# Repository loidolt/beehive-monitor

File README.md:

---
published: true
status: complete
date: 12/20/2016
tags: Electronics Outdoors
description: Beehive monitor that allows you to see the temperature and humidity of the hive.
slug: beehive-monitor
---

# Beehive Monitor

Beehive monitor that allows you to see the temperature and humidity of the hive.

## Table of Contents

- [Beehive Monitor](#beehive-monitor)
  - [Table of Contents](#table-of-contents)
  - [General Info](#general-info)
  - [Technologies](#technologies)

## General Info

This is is a beehive monitor that allows you to see the temperature and humidity of the hive. It also shows the general health of the hive using an LED strip based on ideal temperature and humidity values.

There are two temperature probes, one at the top of the hive and one that can be placed down by the hive ball to get a more accurate reading of the bees themselves. The temperature sensor at the top of the hive is also responsible for measuring humidity.

Sensor data is gathered once a minute, additionally, a rolling thirty-minute average is generated based on this data.

## Technologies
- SketchUp
- Eagle
- KiCAD
- Arduino

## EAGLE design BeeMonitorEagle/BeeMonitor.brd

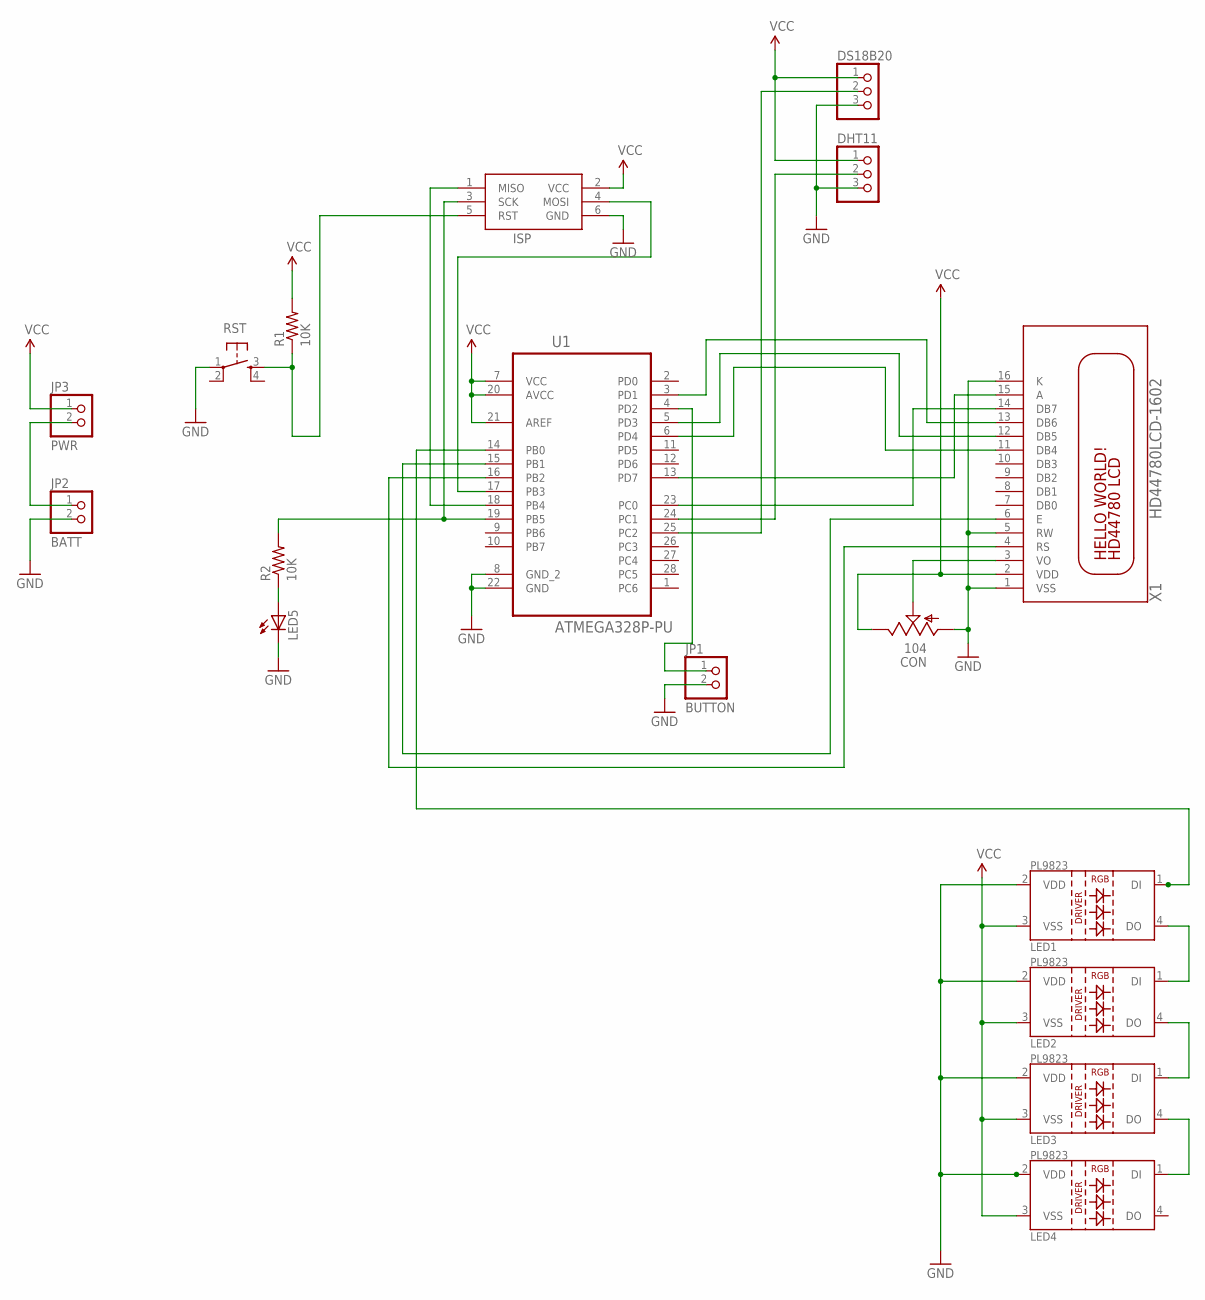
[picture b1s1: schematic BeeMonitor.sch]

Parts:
CON: 104; 6MM
DHT11: PINHD-1X3; 1X03
DS18B20: PINHD-1X3; 1X03
ISP: AVRISP-6; AVRISP
JP1: BUTTON; 1X02
JP2: BATT; 1X02
JP3: PWR; 1X02
LED1, LED2, LED3, LED4: LED-PL9823-F5
LED5: LED3MM
R1, R2: 10K; 0207/10
RST: TAC_SWITCHPTH; TACTILE-PTH
U1: ATMEGA328P-PU; DIP254P762X457-28
X1: HD44780LCD-1602; LCD1602

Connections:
GND: DHT11.3, DS18B20.3, ISP.6 (GND), JP1.2, JP2.2, LED1.2 (VDD), LED2.2 (VDD), LED3.2 (VDD), LED4.2 (VDD), LED5.K (C), RST.1, U1.8 (GND_2), U1.22 (GND)
unnamed: CON.S, X1.3 (VO)
unnamed: ISP.5 (RST), R1.1, RST.3
unnamed: ISP.3 (SCK), R2.2, U1.19 (PB5)
unnamed: ISP.1 (MISO), U1.18 (PB4)
unnamed: ISP.4 (MOSI), U1.17 (PB3)
unnamed: LED1.4 (DO), LED2.1 (DI)
unnamed: LED2.4 (DO), LED3.1 (DI)
unnamed: LED3.4 (DO), LED4.1 (DI)
unnamed: LED1.1 (DI), U1.14 (PB0)
unnamed: U1.3 (PD1), X1.13 (DB6)
unnamed: DHT11.2, U1.24 (PC1)
unnamed: DS18B20.2, U1.25 (PC2)
unnamed: JP1.1, U1.4 (PD2)
unnamed: U1.13 (PD7), X1.15 (A)
unnamed: U1.23 (PC0), X1.14 (DB7)
unnamed: U1.5 (PD3), X1.12 (DB5)
unnamed: U1.6 (PD4), X1.11 (DB4)
unnamed: U1.15 (PB1), X1.6 (E)
unnamed: U1.16 (PB2), X1.4 (RS)
unnamed: LED5.A, R2.1
unnamed: JP2.1, JP3.2
VCC: DHT11.1, DS18B20.1, ISP.2 (VCC), JP3.1, LED1.3 (VSS), LED2.3 (VSS), LED3.3 (VSS), LED4.3 (VSS), R1.2, U1.7 (VCC), U1.20 (AVCC), U1.21 (AREF)
VDD: CON.E, X1.2 (VDD)
VSS: CON.A, X1.1 (VSS), X1.5 (RW), X1.16 (K)

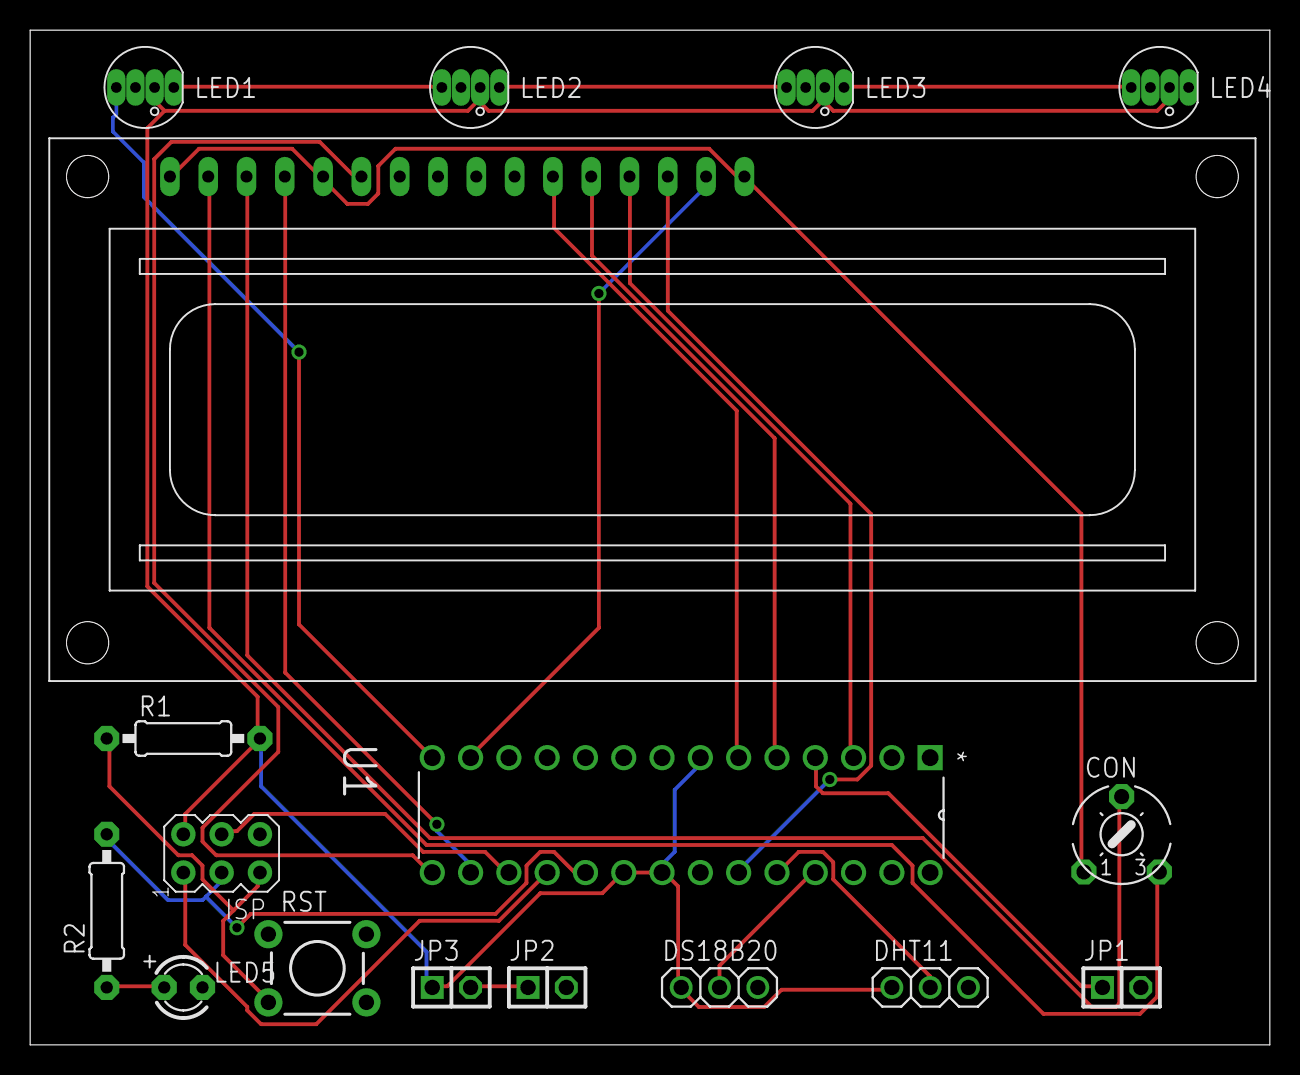
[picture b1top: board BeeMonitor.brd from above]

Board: 2 copper layers, 82.2 x 67.3 mm, 17 parts (0 on the bottom side), 25 nets.

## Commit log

2022-08-28 Re-structure repo

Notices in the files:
parts and their libraries:
SparkFun-Aesthetics: Licensing: Creative Commons ShareAlike 4.0 International - https://creativecommons.org/licenses/by-sa/4.0
